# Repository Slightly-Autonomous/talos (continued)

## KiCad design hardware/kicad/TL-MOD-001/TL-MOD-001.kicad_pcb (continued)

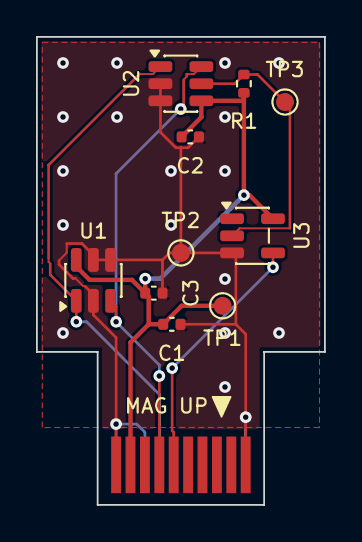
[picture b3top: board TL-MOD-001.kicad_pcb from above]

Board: 2 copper layers, 16.0 x 26.0 mm, 11 parts (0 on the bottom side), 6 nets.

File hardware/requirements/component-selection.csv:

function,ref_board,candidate_mpn,manufacturer,package,key_limits_src,standby_src,alternates,why,status
MCU+radio,TL-SN-001,ESP32-H2-MINI-1-H4S,Espressif,module 13.2x16.6 mm,3.0-3.6 V; 802.15.4 TX 123 mA @18 dBm,deep-sleep 7 uA (LP timer+mem),ESP32-H2-MINI-1U-H4S; nRF52840 module (not researched),Thread 1.4 + BLE; 19 GPIO; existing firmware port,proposed
Power mux,TL-SN-001,TPS2121RUXR,TI,VQFN-HR-12 2x2.5,2.8-22 V; 24 V abs; 4.5 A,disabled input 10 uA (product page; unverified),TPS2120 (WCSP),priority switchover + reverse blocking,proposed
Charger,TL-SN-001,BQ25186DLHR,TI,WSON-10 2.2x2.0,VIN 3.6-18 V; OVP 18.5 V; ICHG <= 1 A,IQ_BAT 3 uA typ,BQ25620 (switching); MCP73831 (no power path),power path + battery-absent operation + VINDPM,proposed
3V3 regulator,TL-SN-001,TPS63900DSKR,TI,WSON-10 2.5x2.5,VIN 1.8-5.5 V; >400 mA at 3.3 V,IQ 75 nA,TPS63802 (higher Iq),lowest Iq buck-boost across 3.0-4.9 V SYS,proposed
Slot load switch,TL-SN-001,TPS22917DBVR,TI,SOT-23-6,1-5.5 V; 2 A; 80 mOhm,IQ 0.5 uA on; ISD 10 nA off,TPS22916 (WCSP),SOT-23 assembly; QOD; ultra-low leakage,proposed
I2C switch,TL-SN-001,TCA9546APWR,TI,TSSOP-16,1.65-5.5 V,standby 1.0 uA typ,PCA9546A,one isolated branch per slot,proposed
GPIO expander,TL-SN-001,TCA9535PWR (x2),TI,TSSOP-24,1.65-5.5 V,standby 0.9 uA typ,PCAL6416A (has pull-ups+masks; not researched),16 I/O + open-drain INT,proposed
UART mux,TL-SN-001,TS3A5017RSVR,TI,UQFN-16,dual SP4T,(not sourced),SN74CBT3253,one UART to four slots,proposed
USB ESD,TL-SN-001,USBLC6-2SC6,ST,SOT-23-6,,(not sourced),TPD2E2U06,KiCad library part,proposed
PV TVS,TL-SN-001,SMAJ12A,various,SMA,12 V standoff,,SMAJ15A,clamp below TPS2121 24 V abs max,proposed (check Voc)
PV reverse,TL-SN-001,SS34,various,SMA,40 V 3 A,,ideal-diode controller (Rev B),simple reverse-polarity block,proposed
Slot connector,TL-SN-001 / TL-DBG-001,HSEC8-110-01-S-D-EM2,Samtec,edge mount 0.80 mm 2x10,30 µin gold; 1.57 mm card,,MEC8-110-02-L-D-EM2 (10 µin only); ERM8/ERF8 EM pair (JLC-stocked),thicker gold for outdoor fretting; same pinout (HW-0007),decided 2026-11-17; footprint from Samtec drawing 2026-11-18 (sample check needed)
3-axis Hall,TL-MOD-001,TMAG5273A1QDBVR,TI,SOT-23-6,1.7-3.6 V; I2C 0x35; +/-40/80 mT; INT open-drain active-low,W&S 1.21 uA @5 s (SRC); ~2.9 uA @100 ms 1 axis (EST); standby 0.45 mA,SM351LT (in-plane AMR switch); DRV5032FB (z-axis only),orientation-independent contact sensing (HW-0006),proposed
INT inverter,TL-MOD-001,SN74AUP1G04DBVR,TI,SOT-23-5,0.8-3.6 V,ICC 0.5 uA max 25 C (0.9 uA -40..85 C),74LVC1G04,turns TMAG5273 INT_N into idle-low push-pull WAKE,proposed
PIR,TL-MOD-002,EKMB1101111,Panasonic,TO-5 3-pin THT,Vdd 2.3-4.0 V; Iout <= 100 uA,Iw 1.0 uA typ,EKMB1201111 (2 uA),1 uA digital-output PIR,proposed
Accelerometer,TL-MOD-003,LIS2DW12TR,ST,LGA-12 2x2,1.62-3.6 V,power-down 50 nA,LIS2DH12,wake/tap engine; sub-uA,proposed
Temp/RH,TL-MOD-004,SHT40-AD1B,Sensirion,DFN-4 1.5x1.5,KiCad SHT4x symbol,(not sourced),SHT45,I2C 0x44,proposed
ID EEPROM,all cards,24AA025E48T-I/OT,Microchip,SOT-23-6,,(not sourced),24AA02E48,factory EUI-48 per card,proposed
USB debug bridge,TL-DBG-001,MCP2221AT-I/SL,Microchip,SOIC-14,USB FS to I2C/UART + 4 GPIO; VDD 3.0-5.5 V (DS20005565E),,CP2112 (I2C only); FT260,no firmware; JLC-stocked; GP1 interrupt-on-change for WAKE,designed

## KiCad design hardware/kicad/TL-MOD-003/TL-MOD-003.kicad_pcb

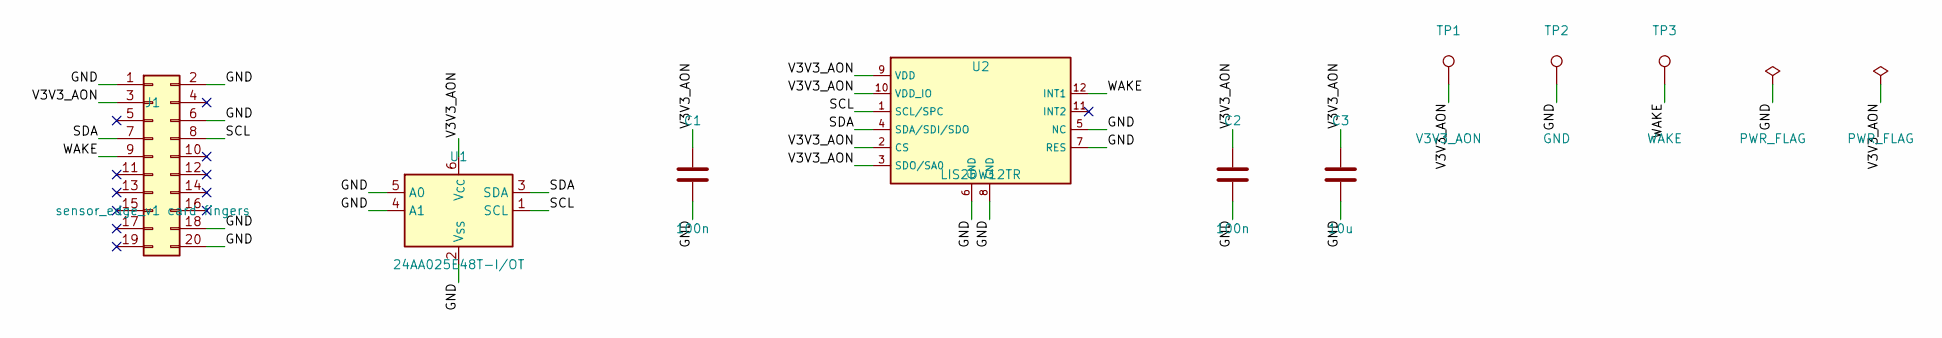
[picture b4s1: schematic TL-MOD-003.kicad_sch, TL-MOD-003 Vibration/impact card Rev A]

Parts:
C1, C2: 100n; C_0402_1005Metric
C3: 10u; C_0805_2012Metric
J1: sensor_edge_v1 card fingers; CardEdge_sensor_edge_v1_2x10_P0.8mm
TP1: V3V3_AON; TestPoint_Pad_D1.0mm
TP2: GND; TestPoint_Pad_D1.0mm
TP3: WAKE; TestPoint_Pad_D1.0mm
U1: 24AA025E48T-I/OT; SOT-23-6
U2: LIS2DW12TR; LGA-12_2x2mm_P0.5mm

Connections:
/GND: C1.2, C2.2, C3.2, J1.1, J1.2, J1.6, J1.18, J1.20, TP2.1, U1.2 (V_{SS}), U1.4 (A1), U1.5 (A0), U2.5 (NC), U2.6 (GND), U2.7 (RES), U2.8 (GND)
/SCL: J1.8, U1.1 (SCL), U2.1 (SCL/SPC)
/SDA: J1.7, U1.3 (SDA), U2.4 (SDA/SDI/SDO)
/V3V3_AON: C1.1, C2.1, C3.1, J1.3, TP1.1, U1.6 (V_{CC}), U2.2 (CS), U2.3 (SDO/SA0), U2.9 (VDD), U2.10 (VDD_IO)
/WAKE: J1.9, TP3.1, U2.12 (INT1)

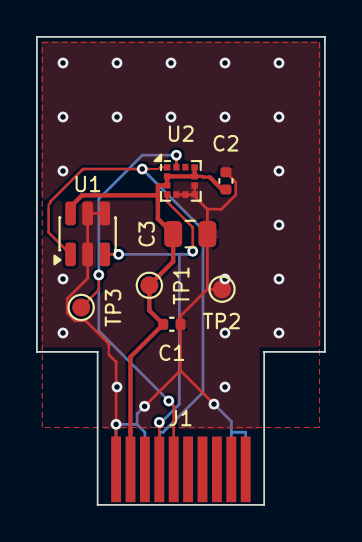
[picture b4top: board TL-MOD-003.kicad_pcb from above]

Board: 2 copper layers, 16.0 x 26.0 mm, 9 parts (0 on the bottom side), 5 nets.

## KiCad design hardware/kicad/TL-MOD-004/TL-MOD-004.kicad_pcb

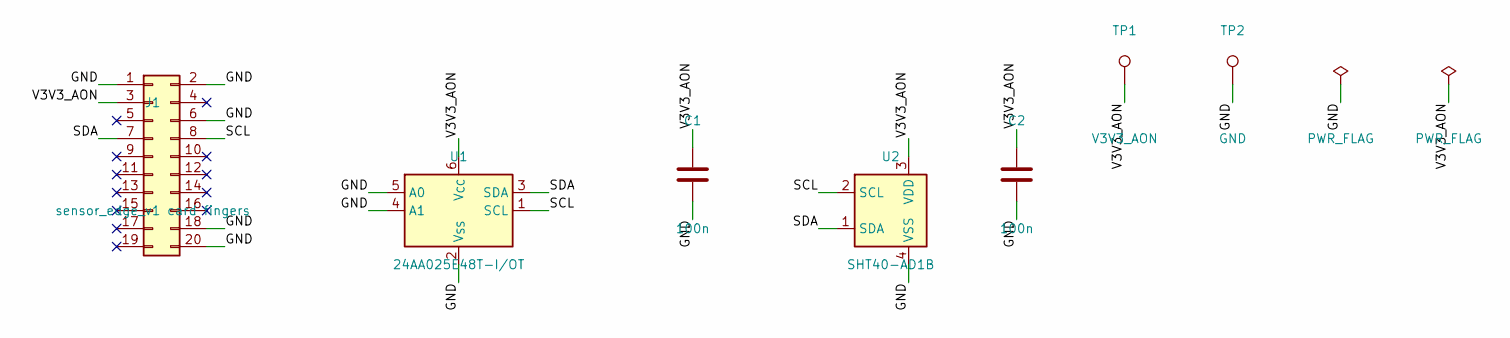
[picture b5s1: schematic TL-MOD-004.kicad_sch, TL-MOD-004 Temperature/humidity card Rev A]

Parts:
C1, C2: 100n; C_0402_1005Metric
J1: sensor_edge_v1 card fingers; CardEdge_sensor_edge_v1_2x10_P0.8mm
TP1: V3V3_AON; TestPoint_Pad_D1.0mm
TP2: GND; TestPoint_Pad_D1.0mm
U1: 24AA025E48T-I/OT; SOT-23-6
U2: SHT40-AD1B; Sensirion_DFN-4_1.5x1.5mm_P0.8mm_SHT4x_CentralKeepout

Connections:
/GND: C1.2, C2.2, J1.1, J1.2, J1.6, J1.18, J1.20, TP2.1, U1.2 (V_{SS}), U1.4 (A1), U1.5 (A0), U2.4 (VSS)
/SCL: J1.8, U1.1 (SCL), U2.2 (SCL)
/SDA: J1.7, U1.3 (SDA), U2.1 (SDA)
/V3V3_AON: C1.1, C2.1, J1.3, TP1.1, U1.6 (V_{CC}), U2.3 (VDD)

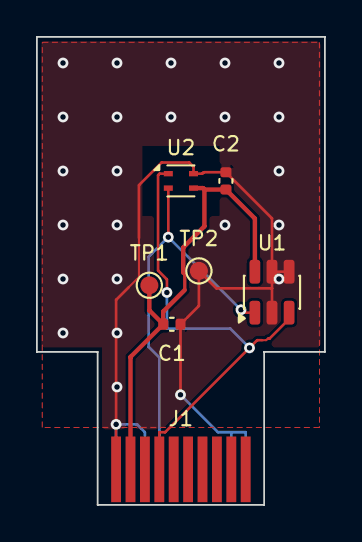
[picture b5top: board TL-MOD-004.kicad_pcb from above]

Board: 2 copper layers, 16.0 x 26.0 mm, 7 parts (0 on the bottom side), 4 nets.

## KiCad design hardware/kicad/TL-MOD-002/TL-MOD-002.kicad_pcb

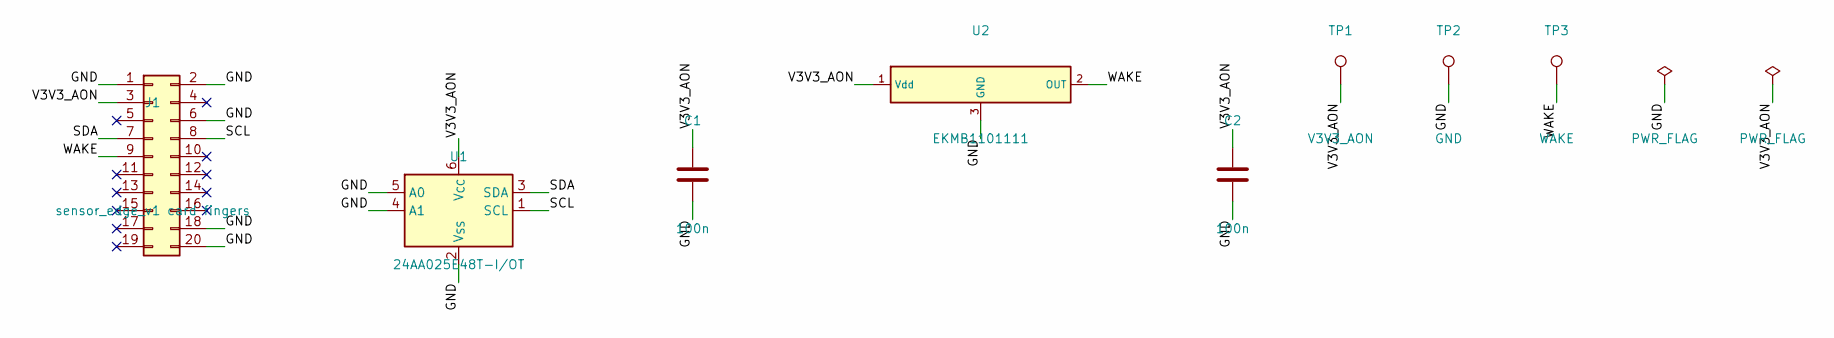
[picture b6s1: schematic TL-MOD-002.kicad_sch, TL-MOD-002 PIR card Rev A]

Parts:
C1, C2: 100n; C_0402_1005Metric
J1: sensor_edge_v1 card fingers; CardEdge_sensor_edge_v1_2x10_P0.8mm
TP1: V3V3_AON; TestPoint_Pad_D1.0mm
TP2: GND; TestPoint_Pad_D1.0mm
TP3: WAKE; TestPoint_Pad_D1.0mm
U1: 24AA025E48T-I/OT; SOT-23-6
U2: EKMB1101111; PIR_Panasonic_EKMB_TO-5

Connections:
/GND: C1.2, C2.2, J1.1, J1.2, J1.6, J1.18, J1.20, TP2.1, U1.2 (V_{SS}), U1.4 (A1), U1.5 (A0), U2.3 (GND)
/SCL: J1.8, U1.1 (SCL)
/SDA: J1.7, U1.3 (SDA)
/V3V3_AON: C1.1, C2.1, J1.3, TP1.1, U1.6 (V_{CC}), U2.1 (Vdd)
/WAKE: J1.9, TP3.1, U2.2 (OUT)

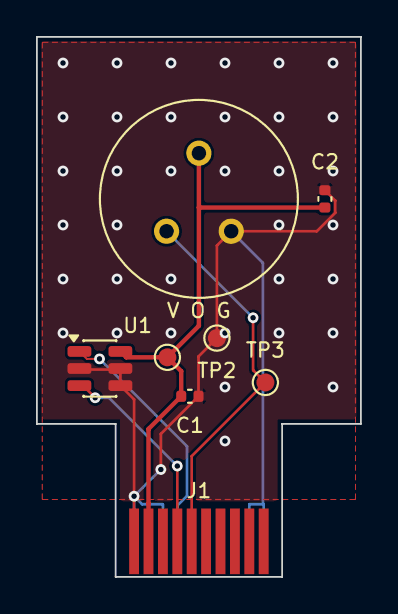
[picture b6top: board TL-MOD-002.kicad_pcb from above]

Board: 2 copper layers, 18.0 x 30.0 mm, 8 parts (0 on the bottom side), 5 nets.

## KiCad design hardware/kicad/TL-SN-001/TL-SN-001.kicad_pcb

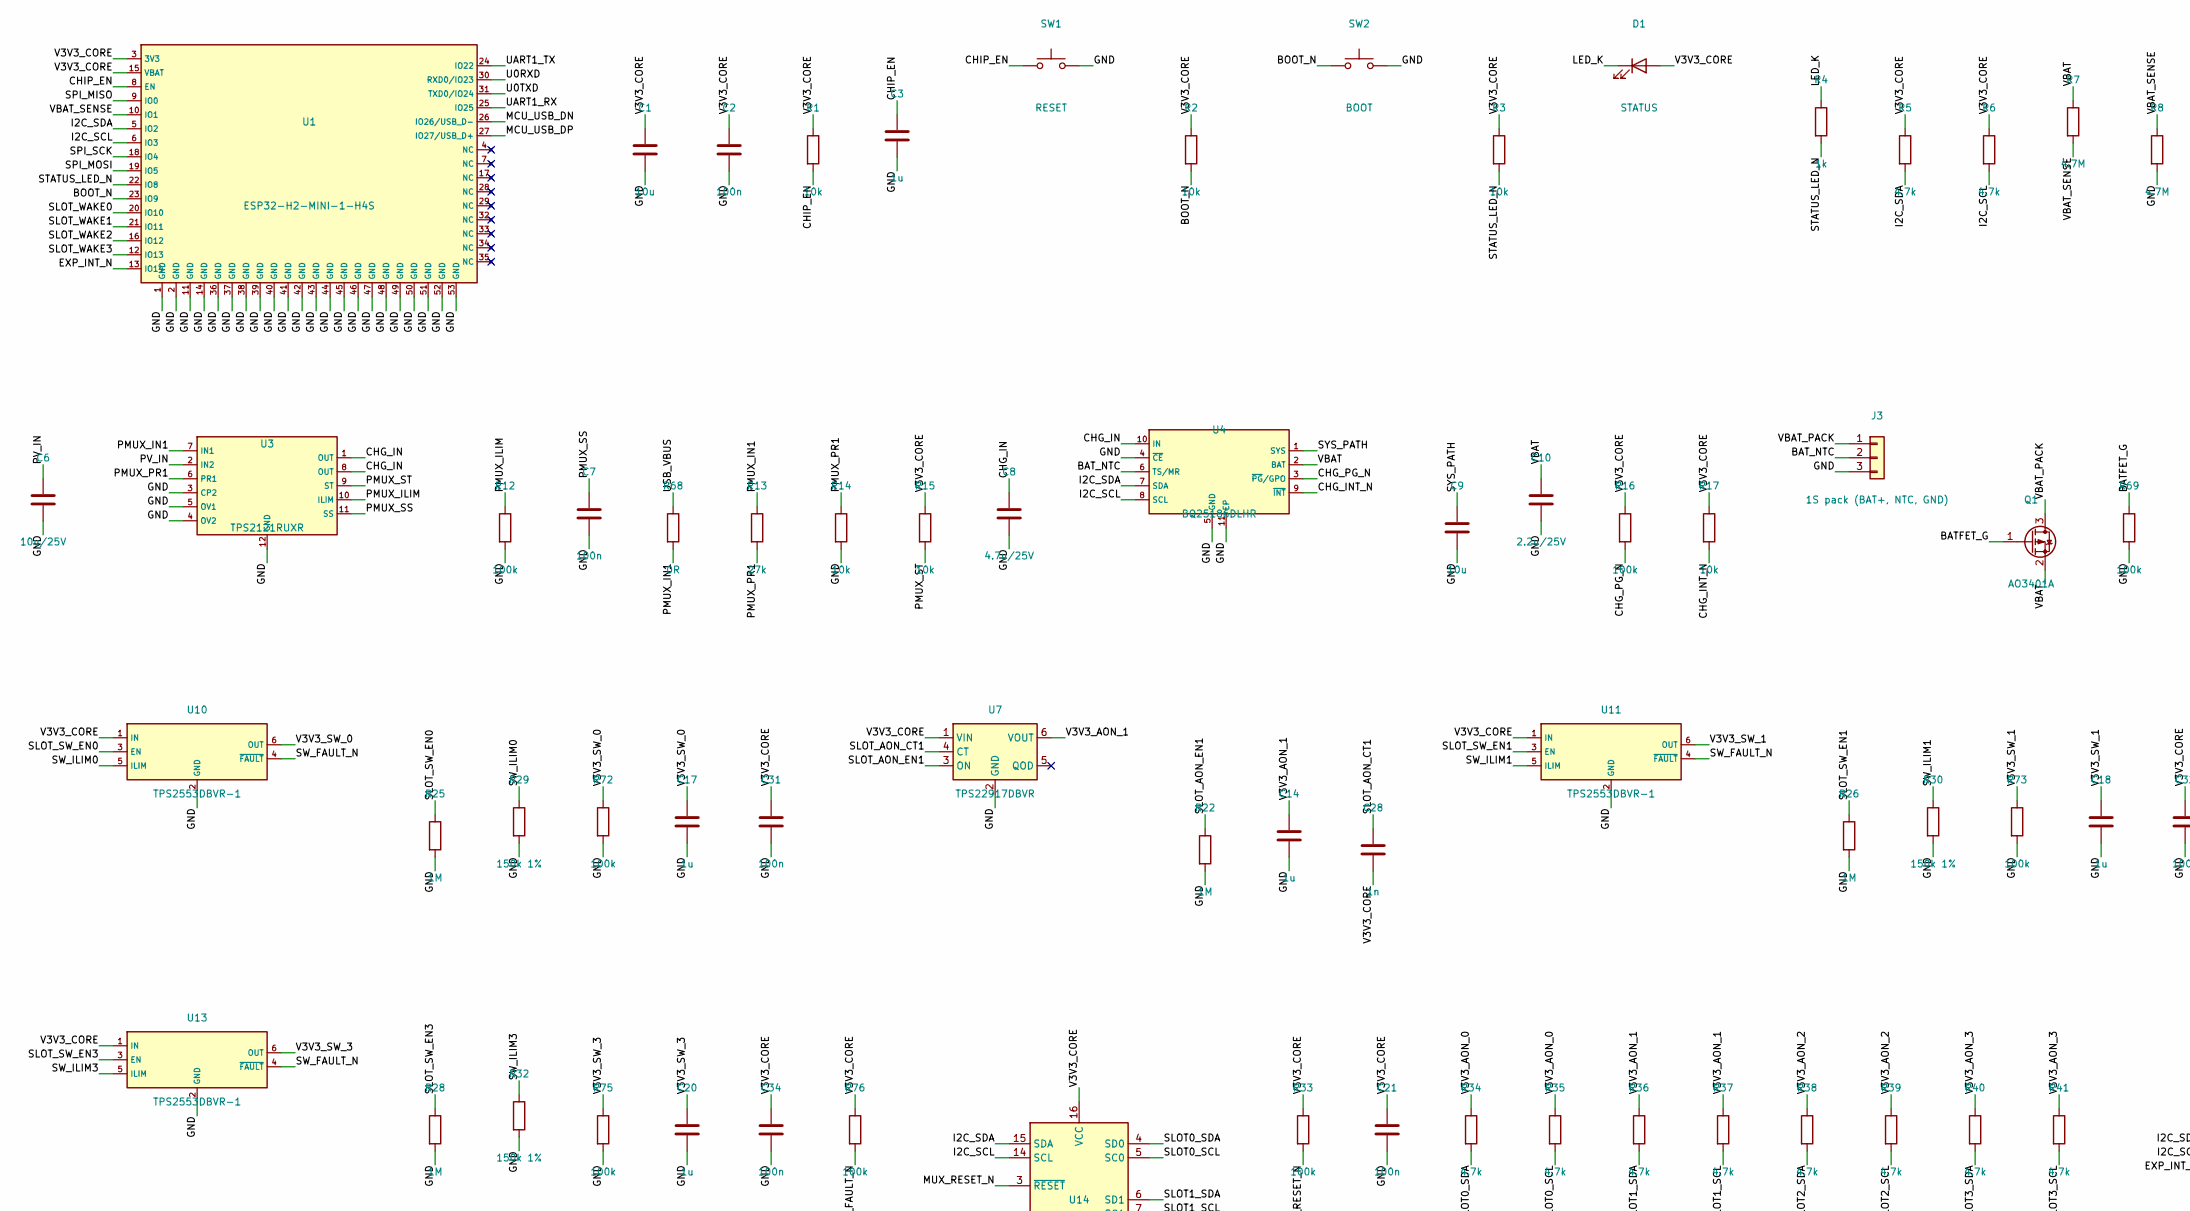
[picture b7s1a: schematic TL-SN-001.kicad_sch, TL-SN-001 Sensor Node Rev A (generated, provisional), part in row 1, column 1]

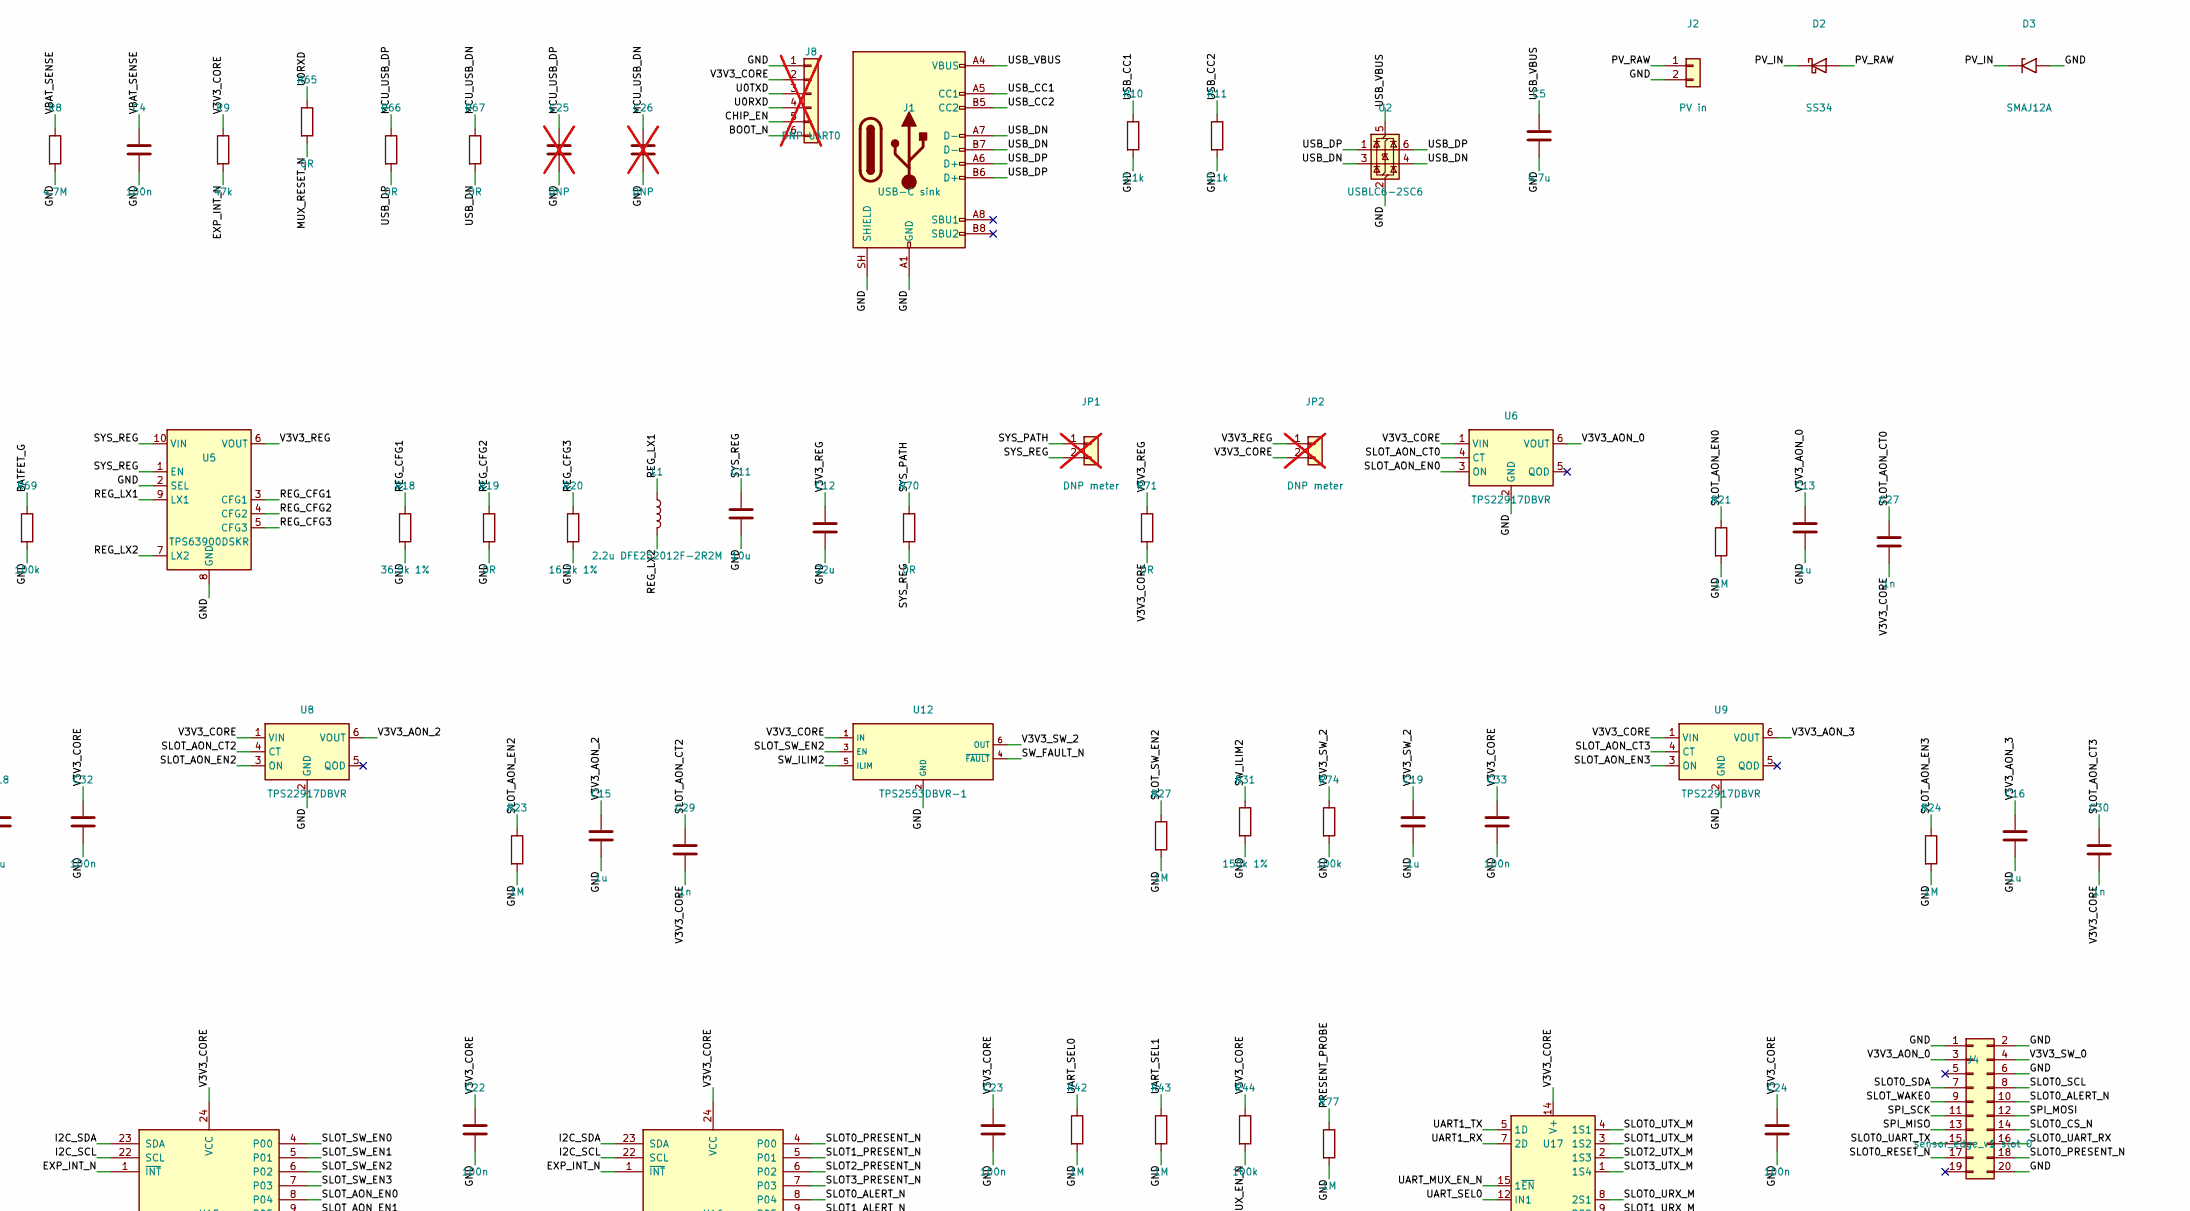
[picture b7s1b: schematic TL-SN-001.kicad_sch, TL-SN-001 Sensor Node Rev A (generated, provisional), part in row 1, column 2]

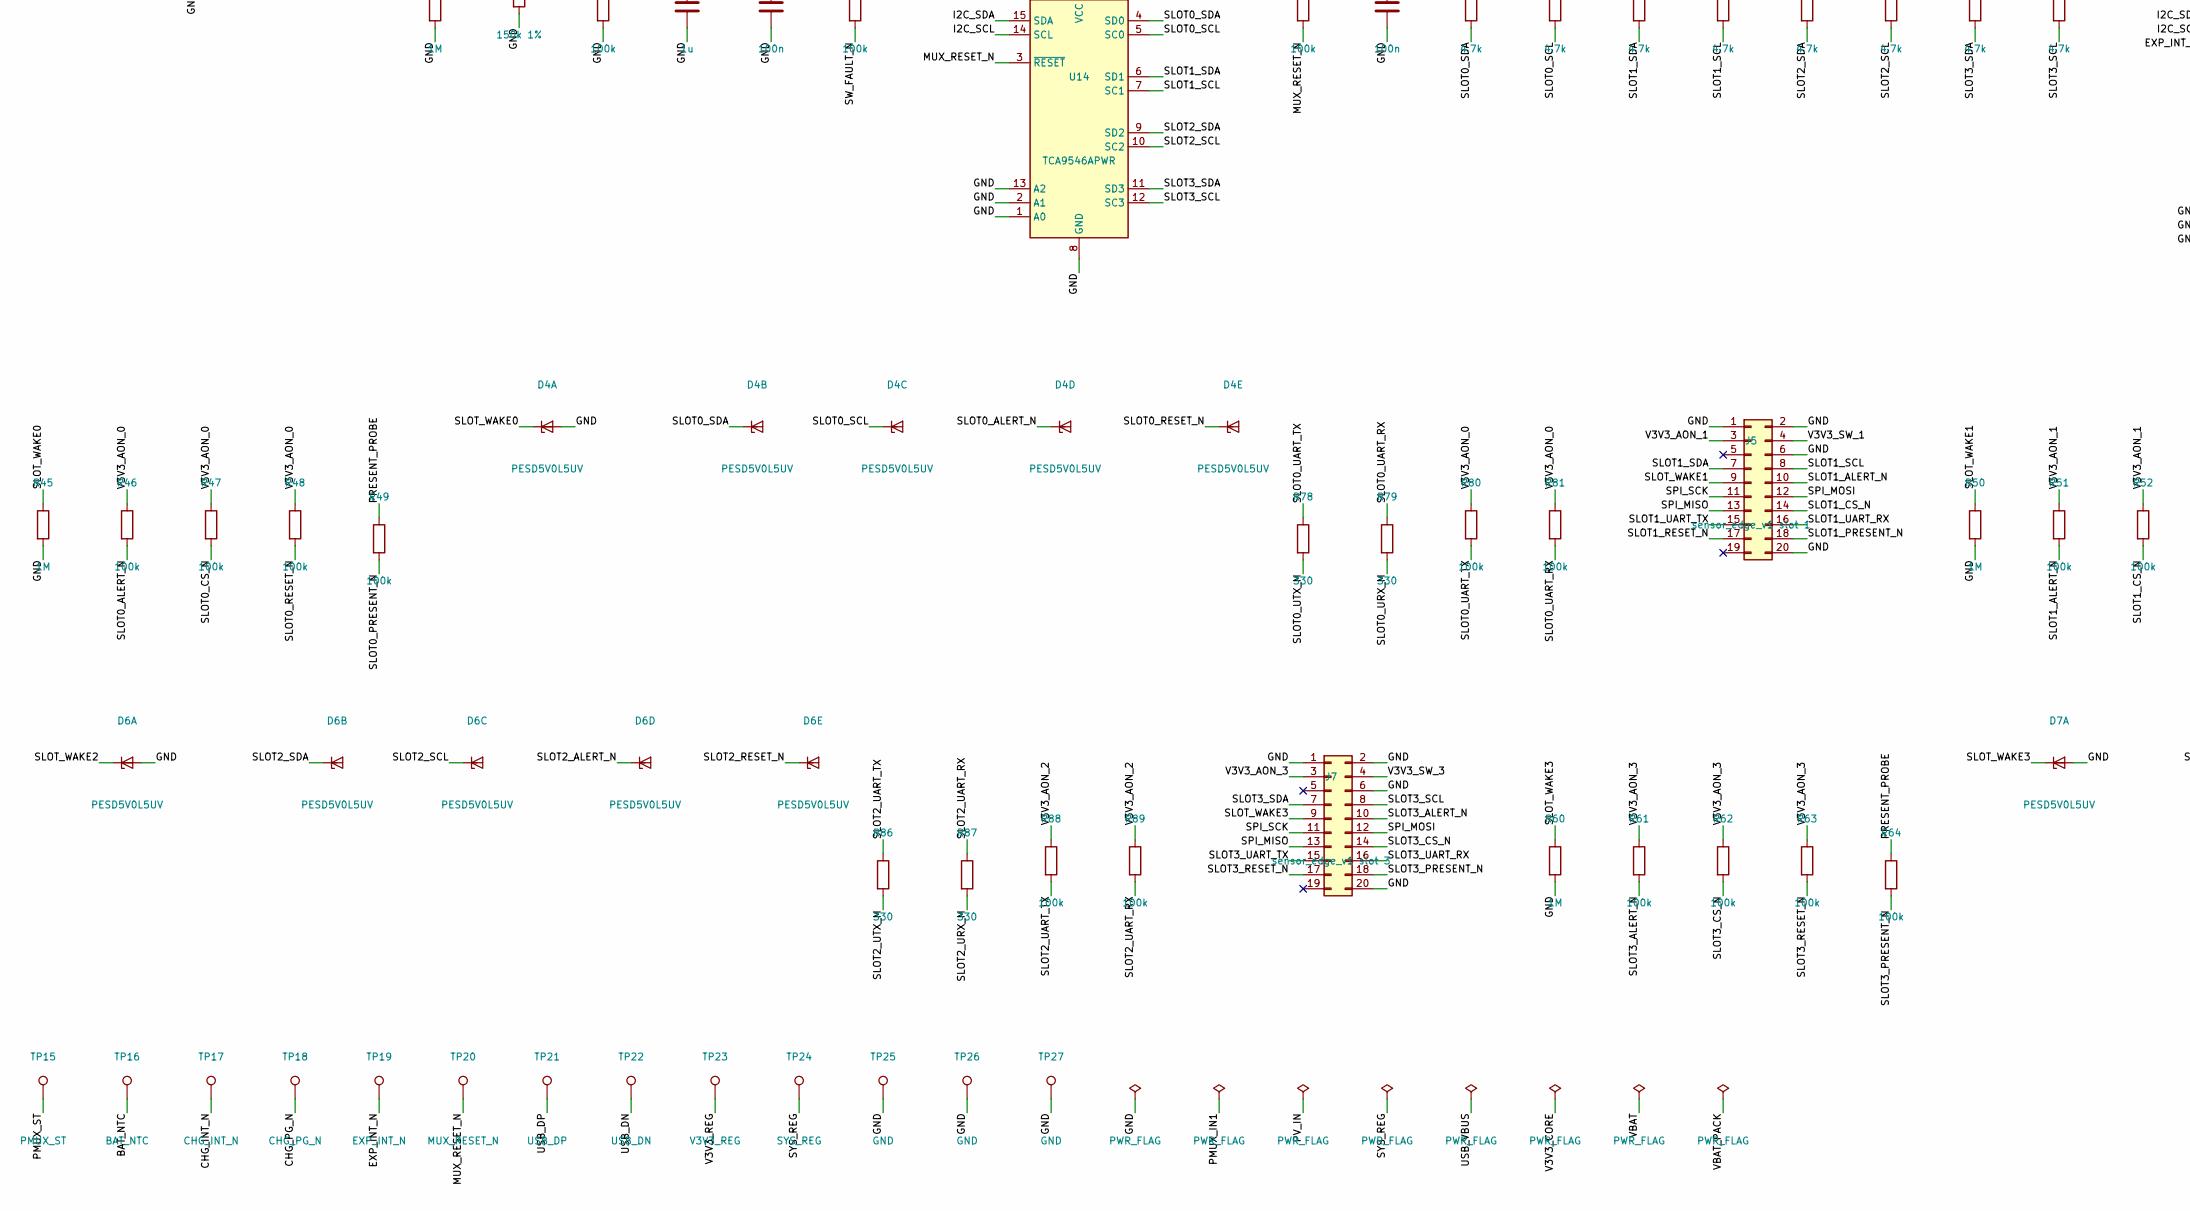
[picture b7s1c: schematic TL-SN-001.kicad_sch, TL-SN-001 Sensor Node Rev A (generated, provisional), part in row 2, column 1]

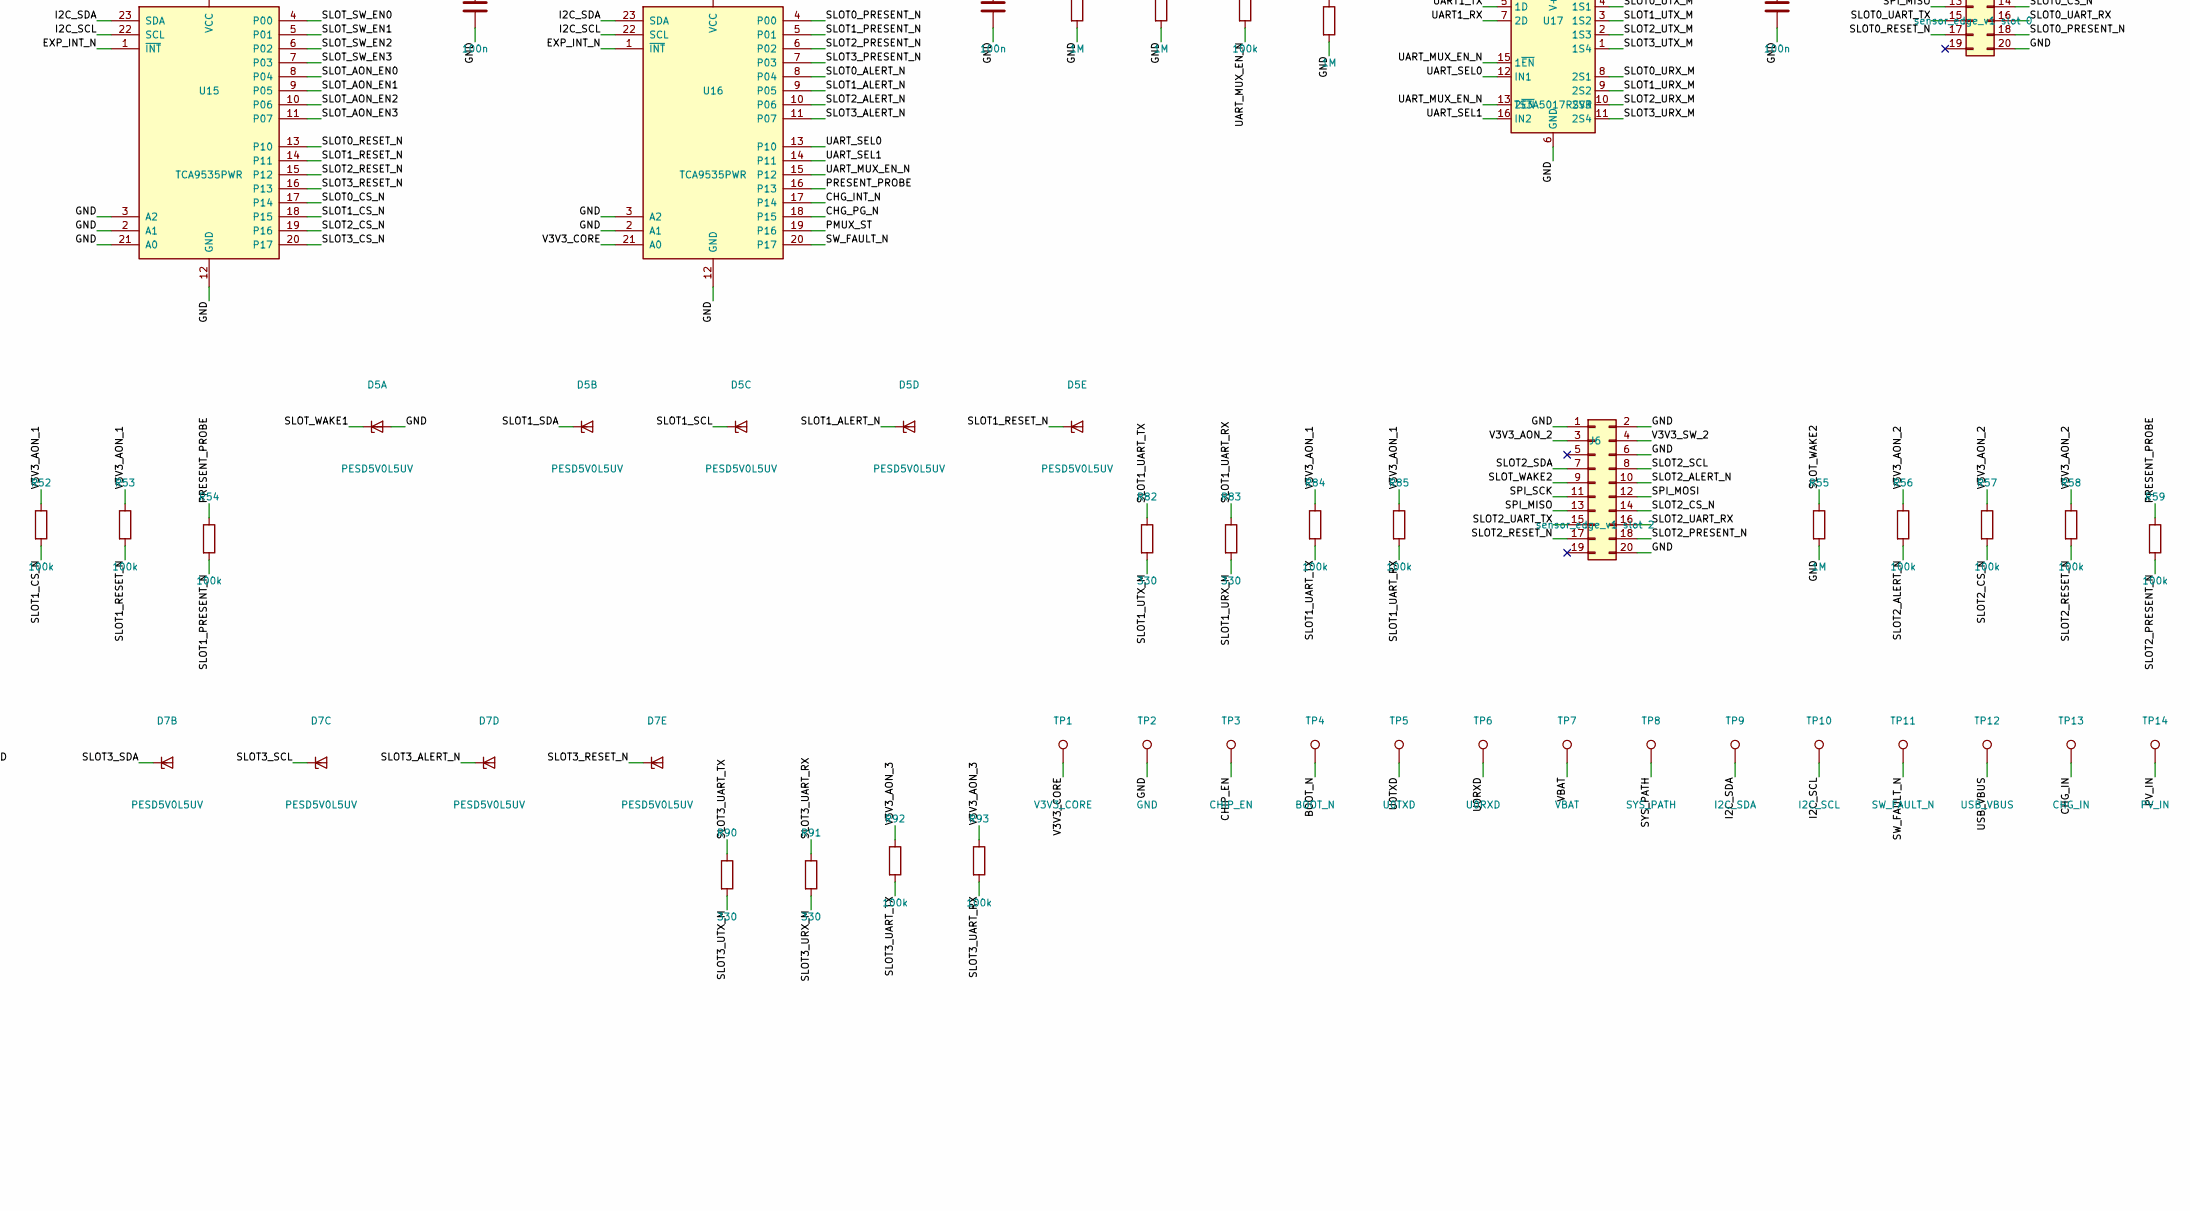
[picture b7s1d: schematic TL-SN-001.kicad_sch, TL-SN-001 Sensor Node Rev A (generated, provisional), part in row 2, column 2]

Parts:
C1, C9, C11: 10u; C_0805_2012Metric
C2, C4, C7, C21, C22, C23, C24, C31, C32, C33, C34: 100n; C_0402_1005Metric
C3, C13, C14, C15, C16, C17, C18, C19, C20: 1u; C_0402_1005Metric
C5: 4.7u; C_0805_2012Metric
C6: 10u/25V; C_0805_2012Metric
C8: 4.7u/25V; C_0805_2012Metric
C10: 2.2u/25V; C_0805_2012Metric
C12: 22u; C_0805_2012Metric
C25, C26: DNP; C_0402_1005Metric; not fitted
C27, C28, C29, C30: 1n; C_0402_1005Metric
D1: STATUS; LED_0603_1608Metric
D2: SS34; D_SMA
D3: SMAJ12A; D_SMA
D4, D5, D6, D7: PESD5V0L5UV; SOT-666
J1: USB-C sink; USB_C_Receptacle_GCT_USB4105-xx-A_16P_TopMnt_Horizontal
J2: PV in; JST_PH_S2B-PH-SM4-TB_1x02-1MP_P2.00mm_Horizontal
J3: 1S pack (BAT+, NTC, GND); JST_PH_S3B-PH-SM4-TB_1x03-1MP_P2.00mm_Horizontal
J4: sensor_edge_v1 slot 0; Samtec_HSEC8-110-01-S-D-EM2
J5: sensor_edge_v1 slot 1; Samtec_HSEC8-110-01-S-D-EM2
J6: sensor_edge_v1 slot 2; Samtec_HSEC8-110-01-S-D-EM2
J7: sensor_edge_v1 slot 3; Samtec_HSEC8-110-01-S-D-EM2
J8: DNP UART0; PinHeader_1x06_P2.54mm_Vertical; not fitted
JP1, JP2: DNP meter; PinHeader_1x02_P2.54mm_Vertical; not fitted
L1: 2.2u DFE252012F-2R2M; L_1008_2520Metric
Q1: AO3401A; SOT-23
R1, R2, R3, R14, R15, R17: 10k; R_0402_1005Metric
R4: 1k; R_0402_1005Metric
R5, R6, R34, R35, R36, R37, R38, R39, R40, R41: 4.7k; R_0402_1005Metric
R7, R8: 4.7M; R_0402_1005Metric
R9: 47k; R_0402_1005Metric
R10, R11: 5.1k; R_0402_1005Metric
R12, R16, R33, R44, R46, R47, R48, R49, R51, R52, R53, R54, R56, R57, R58, R59, R61, R62, R63, R64, R69, R72, R73, R74, R75, R76, R80, R81, R84, R85, R88, R89, R92, R93: 100k; R_0402_1005Metric
R13: 27k; R_0402_1005Metric
R18: 36.5k 1%; R_0402_1005Metric
R19, R65, R66, R67: 0R; R_0402_1005Metric
R20: 16.2k 1%; R_0402_1005Metric
R21, R22, R23, R24, R25, R26, R27, R28, R42, R43, R45, R50, R55, R60, R77: 1M; R_0402_1005Metric
R29, R30, R31, R32: 150k 1%; R_0402_1005Metric
R68, R70, R71: 0R; R_0805_2012Metric
R78, R79, R82, R83, R86, R87, R90, R91: 330; R_0402_1005Metric
SW1: RESET; SW_SPST_PTS810
SW2: BOOT; SW_SPST_PTS810
TP1: V3V3_CORE; TestPoint_Pad_D1.0mm
TP2, TP25, TP26, TP27: GND; TestPoint_Pad_D1.0mm
TP3: CHIP_EN; TestPoint_Pad_D1.0mm
TP4: BOOT_N; TestPoint_Pad_D1.0mm
TP5: U0TXD; TestPoint_Pad_D1.0mm
TP6: U0RXD; TestPoint_Pad_D1.0mm
TP7: VBAT; TestPoint_Pad_D1.0mm
TP8: SYS_PATH; TestPoint_Pad_D1.0mm
TP9: I2C_SDA; TestPoint_Pad_D1.0mm
TP10: I2C_SCL; TestPoint_Pad_D1.0mm
TP11: SW_FAULT_N; TestPoint_Pad_D1.0mm
TP12: USB_VBUS; TestPoint_Pad_D1.0mm
TP13: CHG_IN; TestPoint_Pad_D1.0mm
TP14: PV_IN; TestPoint_Pad_D1.0mm
TP15: PMUX_ST; TestPoint_Pad_D1.0mm
TP16: BAT_NTC; TestPoint_Pad_D1.0mm
TP17: CHG_INT_N; TestPoint_Pad_D1.0mm
TP18: CHG_PG_N; TestPoint_Pad_D1.0mm
TP19: EXP_INT_N; TestPoint_Pad_D1.0mm
TP20: MUX_RESET_N; TestPoint_Pad_D1.0mm
TP21: USB_DP; TestPoint_Pad_D1.0mm
TP22: USB_DN; TestPoint_Pad_D1.0mm
TP23: V3V3_REG; TestPoint_Pad_D1.0mm
TP24: SYS_REG; TestPoint_Pad_D1.0mm
U1: ESP32-H2-MINI-1-H4S; ESP32-H2-MINI-1
U2: USBLC6-2SC6; SOT-23-6
U3: TPS2121RUXR; Texas_VQFN-HR-12_2x2.5mm_P0.5mm
U4: BQ25186DLHR; Texas_DLH0010A_WSON-10-1EP_2.2x2mm_P0.4mm
U5: TPS63900DSKR; WSON-10-1EP_2.5x2.5mm_P0.5mm_EP1.2x2mm
U6, U7, U8, U9: TPS22917DBVR; SOT-23-6
U10, U11, U12, U13: TPS2553DBVR-1; SOT-23-6
U14: TCA9546APWR; TSSOP-16_4.4x5mm_P0.65mm
U15, U16: TCA9535PWR; TSSOP-24_4.4x7.8mm_P0.65mm
U17: TS3A5017RSVR; UQFN-16_1.8x2.6mm_P0.4mm

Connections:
/BATFET_G: Q1.1 (G), R69.1
/BAT_NTC: J3.2, TP16.1, U4.6 (TS/MR)
/BOOT_N: J8.6, R2.2, SW2.1, TP4.1, U1.23 (IO9)
/CHG_IN: C8.1, TP13.1, U3.1 (OUT), U3.8 (OUT), U4.10 (IN)
/CHG_INT_N: R17.2, TP17.1, U4.9 (~INT), U16.17 (P14)
/CHG_PG_N: R16.2, TP18.1, U4.3 (~PG/GPO), U16.18 (P15)
/CHIP_EN: C3.1, J8.5, R1.2, SW1.1, TP3.1, U1.8 (EN)
/EXP_INT_N: R9.2, TP19.1, U1.13 (IO14), U15.1 (~INT), U16.1 (~INT)
/GND: C1.2, C2.2, C3.2, C4.2, C5.2, C6.2, C7.2, C8.2, C9.2, C10.2, C11.2, C12.2, C13.2, C14.2, C15.2, C16.2, C17.2, C18.2, C19.2, C20.2, C21.2, C22.2, C23.2, C24.2, C25.2, C26.2, C31.2, C32.2, C33.2, C34.2, D3.2 (A2), D4.2 (A), D5.2 (A), D6.2 (A), D7.2 (A), J1.A1 (GND), J1.A12 (GND), J1.B1 (GND), J1.B12 (GND), J1.SH (SHIELD), J2.2, J3.3, J4.1, J4.2, J4.6, J4.20, J5.1, J5.2, J5.6, J5.20, J6.1, J6.2, J6.6, J6.20, J7.1, J7.2, J7.6, J7.20, J8.1, R8.2, R10.2, R11.2, R12.2, R14.2, R18.2, R19.2, R20.2, R21.2, R22.2, R23.2, R24.2, R25.2, R26.2, R27.2, R28.2, R29.2, R30.2, R31.2, R32.2, R42.2, R43.2, R45.2, R50.2, R55.2, R60.2, R69.2, R72.2, R73.2, R74.2, R75.2, R77.2, SW1.2, SW2.2, TP2.1, TP25.1, TP26.1, TP27.1, U1.1 (GND), U1.2 (GND), U1.11 (GND), U1.14 (GND), U1.36 (GND), U1.37 (GND), U1.38 (GND), U1.39 (GND), U1.40 (GND), U1.41 (GND), U1.42 (GND), U1.43 (GND), U1.44 (GND), U1.45 (GND), U1.46 (GND), U1.47 (GND), U1.48 (GND), U1.49 (GND), U1.50 (GND), U1.51 (GND), U1.52 (GND), U1.53 (GND), U2.2 (GND), U3.3 (CP2), U3.4 (OV2), U3.5 (OV1), U3.12 (GND), U4.4 (~CE), U4.5 (GND), U4.11 (EP), U5.2 (SEL), U5.8 (GND), U5.11 (GND), U6.2 (GND), U7.2 (GND), U8.2 (GND), U9.2 (GND), U10.2 (GND), U11.2 (GND), U12.2 (GND), U13.2 (GND), U14.1 (A0), U14.2 (A1), U14.8 (GND), U14.13 (A2), U15.2 (A1), U15.3 (A2), U15.12 (GND), U15.21 (A0), U16.2 (A1), U16.3 (A2), U16.12 (GND), U17.6 (GND)
/I2C_SCL: R6.2, TP10.1, U1.6 (IO3), U4.8 (SCL), U14.14 (SCL), U15.22 (SCL), U16.22 (SCL)
/I2C_SDA: R5.2, TP9.1, U1.5 (IO2), U4.7 (SDA), U14.15 (SDA), U15.23 (SDA), U16.23 (SDA)
/LED_K: D1.1 (K), R4.1
/MCU_USB_DN: C26.1, R67.1, U1.26 (IO26/USB_D-)
/MCU_USB_DP: C25.1, R66.1, U1.27 (IO27/USB_D+)
/MUX_RESET_N: R33.2, R65.2, TP20.1, U14.3 (~RESET)
/PMUX_ILIM: R12.1, U3.10 (ILIM)
/PMUX_IN1: R13.1, R68.2, U3.7 (IN1)
/PMUX_PR1: R13.2, R14.1, U3.6 (PR1)
/PMUX_SS: C7.1, U3.11 (SS)
/PMUX_ST: R15.2, TP15.1, U3.9 (ST), U16.19 (P16)
/PRESENT_PROBE: R49.1, R54.1, R59.1, R64.1, R77.1, U16.16 (P13)
/PV_IN: C6.1, D2.1 (K), D3.1 (A1), TP14.1, U3.2 (IN2)
/PV_RAW: D2.2 (A), J2.1
/REG_CFG1: R18.1, U5.3 (CFG1)
/REG_CFG2: R19.1, U5.4 (CFG2)
/REG_CFG3: R20.1, U5.5 (CFG3)
/REG_LX1: L1.1, U5.9 (LX1)
/REG_LX2: L1.2, U5.7 (LX2)
/SLOT0_ALERT_N: D4.5 (K4), J4.10, R46.2, U16.8 (P04)
/SLOT0_CS_N: J4.14, R47.2, U15.17 (P14)
/SLOT0_PRESENT_N: J4.18, R49.2, U16.4 (P00)
/SLOT0_RESET_N: D4.6 (K5), J4.17, R48.2, U15.13 (P10)
/SLOT0_SCL: D4.4 (K3), J4.8, R35.2, U14.5 (SC0)
/SLOT0_SDA: D4.3 (K2), J4.7, R34.2, U14.4 (SD0)
/SLOT0_UART_RX: J4.16, R79.1, R81.2
/SLOT0_UART_TX: J4.15, R78.1, R80.2
/SLOT0_URX_M: R79.2, U17.8 (2S1)
/SLOT0_UTX_M: R78.2, U17.4 (1S1)
/SLOT1_ALERT_N: D5.5 (K4), J5.10, R51.2, U16.9 (P05)
/SLOT1_CS_N: J5.14, R52.2, U15.18 (P15)
/SLOT1_PRESENT_N: J5.18, R54.2, U16.5 (P01)
/SLOT1_RESET_N: D5.6 (K5), J5.17, R53.2, U15.14 (P11)
/SLOT1_SCL: D5.4 (K3), J5.8, R37.2, U14.7 (SC1)
/SLOT1_SDA: D5.3 (K2), J5.7, R36.2, U14.6 (SD1)
/SLOT1_UART_RX: J5.16, R83.1, R85.2
/SLOT1_UART_TX: J5.15, R82.1, R84.2
/SLOT1_URX_M: R83.2, U17.9 (2S2)
/SLOT1_UTX_M: R82.2, U17.3 (1S2)
/SLOT2_ALERT_N: D6.5 (K4), J6.10, R56.2, U16.10 (P06)
/SLOT2_CS_N: J6.14, R57.2, U15.19 (P16)
/SLOT2_PRESENT_N: J6.18, R59.2, U16.6 (P02)
/SLOT2_RESET_N: D6.6 (K5), J6.17, R58.2, U15.15 (P12)
/SLOT2_SCL: D6.4 (K3), J6.8, R39.2, U14.10 (SC2)
/SLOT2_SDA: D6.3 (K2), J6.7, R38.2, U14.9 (SD2)
/SLOT2_UART_RX: J6.16, R87.1, R89.2
/SLOT2_UART_TX: J6.15, R86.1, R88.2
/SLOT2_URX_M: R87.2, U17.10 (2S3)
/SLOT2_UTX_M: R86.2, U17.2 (1S3)
/SLOT3_ALERT_N: D7.5 (K4), J7.10, R61.2, U16.11 (P07)
/SLOT3_CS_N: J7.14, R62.2, U15.20 (P17)
/SLOT3_PRESENT_N: J7.18, R64.2, U16.7 (P03)
/SLOT3_RESET_N: D7.6 (K5), J7.17, R63.2, U15.16 (P13)
/SLOT3_SCL: D7.4 (K3), J7.8, R41.2, U14.12 (SC3)
/SLOT3_SDA: D7.3 (K2), J7.7, R40.2, U14.11 (SD3)
/SLOT3_UART_RX: J7.16, R91.1, R93.2
/SLOT3_UART_TX: J7.15, R90.1, R92.2
/SLOT3_URX_M: R91.2, U17.11 (2S4)
/SLOT3_UTX_M: R90.2, U17.1 (1S4)
/SLOT_AON_CT0: C27.1, U6.4 (CT)
/SLOT_AON_CT1: C28.1, U7.4 (CT)
/SLOT_AON_CT2: C29.1, U8.4 (CT)
/SLOT_AON_CT3: C30.1, U9.4 (CT)
/SLOT_AON_EN0: R21.1, U6.3 (ON), U15.8 (P04)
/SLOT_AON_EN1: R22.1, U7.3 (ON), U15.9 (P05)
/SLOT_AON_EN2: R23.1, U8.3 (ON), U15.10 (P06)
/SLOT_AON_EN3: R24.1, U9.3 (ON), U15.11 (P07)
/SLOT_SW_EN0: R25.1, U10.3 (EN), U15.4 (P00)
/SLOT_SW_EN1: R26.1, U11.3 (EN), U15.5 (P01)
/SLOT_SW_EN2: R27.1, U12.3 (EN), U15.6 (P02)
/SLOT_SW_EN3: R28.1, U13.3 (EN), U15.7 (P03)
/SLOT_WAKE0: D4.1 (K1), J4.9, R45.1, U1.20 (IO10)
/SLOT_WAKE1: D5.1 (K1), J5.9, R50.1, U1.21 (IO11)
/SLOT_WAKE2: D6.1 (K1), J6.9, R55.1, U1.16 (IO12)
/SLOT_WAKE3: D7.1 (K1), J7.9, R60.1, U1.12 (IO13)
/SPI_MISO: J4.13, J5.13, J6.13, J7.13, U1.9 (IO0)
/SPI_MOSI: J4.12, J5.12, J6.12, J7.12, U1.19 (IO5)
/SPI_SCK: J4.11, J5.11, J6.11, J7.11, U1.18 (IO4)
/STATUS_LED_N: R3.2, R4.2, U1.22 (IO8)
/SW_FAULT_N: R76.2, TP11.1, U10.4 (~FAULT), U11.4 (~FAULT), U12.4 (~FAULT), U13.4 (~FAULT), U16.20 (P17)
/SW_ILIM0: R29.1, U10.5 (ILIM)
/SW_ILIM1: R30.1, U11.5 (ILIM)
/SW_ILIM2: R31.1, U12.5 (ILIM)
/SW_ILIM3: R32.1, U13.5 (ILIM)
/SYS_PATH: C9.1, JP1.1, R70.1, TP8.1, U4.1 (SYS)
/SYS_REG: C11.1, JP1.2, R70.2, TP24.1, U5.1 (EN), U5.10 (VIN)
/U0RXD: J8.4, R65.1, TP6.1, U1.30 (RXD0/IO23)
/U0TXD: J8.3, TP5.1, U1.31 (TXD0/IO24)
/UART1_RX: U1.25 (IO25), U17.7 (2D)
/UART1_TX: U1.24 (IO22), U17.5 (1D)
/UART_MUX_EN_N: R44.2, U16.15 (P12), U17.13 (2~EN), U17.15 (1~EN)
/UART_SEL0: R42.1, U16.13 (P10), U17.12 (IN1)
/UART_SEL1: R43.1, U16.14 (P11), U17.16 (IN2)
/USB_CC1: J1.A5 (CC1), R10.1
/USB_CC2: J1.B5 (CC2), R11.1
/USB_DN: J1.A7 (D-), J1.B7 (D-), R67.2, TP22.1, U2.3 (I/O2), U2.4 (I/O2)
/USB_DP: J1.A6 (D+), J1.B6 (D+), R66.2, TP21.1, U2.1 (I/O1), U2.6 (I/O1)
/USB_VBUS: C5.1, J1.A4 (VBUS), J1.A9 (VBUS), J1.B4 (VBUS), J1.B9 (VBUS), R68.1, TP12.1, U2.5 (VBUS)
/V3V3_AON_0: C13.1, J4.3, R34.1, R35.1, R46.1, R47.1, R48.1, R80.1, R81.1, U6.6 (VOUT)
/V3V3_AON_1: C14.1, J5.3, R36.1, R37.1, R51.1, R52.1, R53.1, R84.1, R85.1, U7.6 (VOUT)
/V3V3_AON_2: C15.1, J6.3, R38.1, R39.1, R56.1, R57.1, R58.1, R88.1, R89.1, U8.6 (VOUT)
/V3V3_AON_3: C16.1, J7.3, R40.1, R41.1, R61.1, R62.1, R63.1, R92.1, R93.1, U9.6 (VOUT)
/V3V3_CORE: C1.1, C2.1, C21.1, C22.1, C23.1, C24.1, C27.2, C28.2, C29.2, C30.2, C31.1, C32.1, C33.1, C34.1, D1.2 (A), J8.2, JP2.2, R1.1, R2.1, R3.1, R5.1, R6.1, R9.1, R15.1, R16.1, R17.1, R33.1, R44.1, R71.2, R76.1, TP1.1, U1.3 (3V3), U1.15 (VBAT), U6.1 (VIN), U7.1 (VIN), U8.1 (VIN), U9.1 (VIN), U10.1 (IN), U11.1 (IN), U12.1 (IN), U13.1 (IN), U14.16 (VCC), U15.24 (VCC), U16.21 (A0), U16.24 (VCC), U17.14 (V+)
/V3V3_REG: C12.1, JP2.1, R71.1, TP23.1, U5.6 (VOUT)
/V3V3_SW_0: C17.1, J4.4, R72.1, U10.6 (OUT)
/V3V3_SW_1: C18.1, J5.4, R73.1, U11.6 (OUT)
/V3V3_SW_2: C19.1, J6.4, R74.1, U12.6 (OUT)
/V3V3_SW_3: C20.1, J7.4, R75.1, U13.6 (OUT)
/VBAT: C10.1, Q1.2 (S), R7.1, TP7.1, U4.2 (BAT)
/VBAT_PACK: J3.1, Q1.3 (D)
/VBAT_SENSE: C4.1, R7.2, R8.1, U1.10 (IO1)
